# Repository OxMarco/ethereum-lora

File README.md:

# Ethereum LoRa

## Abstract

**Ethereum LoRa is a project aimed at adding a LoRa radio interface to Ethereum nodes.** By doing so, it becomes possible to query a node with JSON-RPC commands even in locations where Wi-Fi or cellular connectivity is absent. This enhancement allows Ethereum-based services to run in rural or underdeveloped areas of the world, fostering crypto adoption.

### About LoRa

The LoRa Communication System is an innovative project designed to facilitate seamless and efficient communication using the LoRa protocol. Aimed at establishing a reliable medium for data transmission even in challenging conditions, our solution stands as a testament to the powerful blend of software ingenuity and hardware capabilities. Whether it's for remote sensing applications, IoT devices, or any scenario where traditional connectivity might falter, our system ensures that your data reaches its destination.

## Technical Details

The software interfaces with the Ethereum node and the LoRa E22 module, allowing bi-directional communication. When the system starts, it sets up the LoRa module with specific configurations. Users can input JSON payloads, which are then sent via the LoRa interface to an Ethereum node. The system also listens for incoming messages from the Ethereum node, which can then be parsed and presented to the user.

### How It Works
At its core, our system relies on the LoRa (Long Range) protocol, a patented digital wireless data communication technology. Through a combination of software controllers and hardware integrations, the system listens for incoming LoRa messages and parses them for further processing. Depending on the message type—whether it's a handshake or a request—the controller can efficiently interpret and respond to the data.

### Assumptions
- The devices used are compatible with the LoRa E22 chip model.
- The data communicated is structured in JSON format with specific fields, such as "message_type", to allow the system to differentiate between different types of messages.
- The environment variables are correctly set for chip model, serial port, and other necessary pins.

### Implementation
We've designed a modular approach, with a main driver program that leverages two key components: the `ConfigManager` and `LoRaController`. The `ConfigManager` handles configuration retrieval while the `LoRaController` manages the setup, listening, and sending of LoRa messages. When data is received, it's parsed based on its message type and, if it's a request, further extracted to ensure clean and valid JSON content.

### Running the Project Locally

1. Ensure you have Python installed (version 3.x recommended).
2. Clone the repository:  
   ```
   git clone <repository_url>
   ```
3. Navigate to the project directory.
4. Install the required libraries:  
   ```
   pip install -r requirements.txt
   ```
5. Set the necessary environment variables (like `LORA_CHIP_MODEL`, `SERIAL_PORT`, etc.).
6. Run the application:  
   ```
   python client.py
   ```
   Or
   ```
   python server.py
   ```

## Hardware
The BOM is very basic, consisting of a LoRa UART module and a simple PCB TTL-to-UART adapter.

Pins at the bottom of the PCB allow users to upgrade the firmware or select a different working mode, for instance to support re-broadcasting, a form of basic mesh networking.

## Acknowledgements
A big thanks goes to the Ethereum Foundation for sponsoring this project under their "Run a Node" program.

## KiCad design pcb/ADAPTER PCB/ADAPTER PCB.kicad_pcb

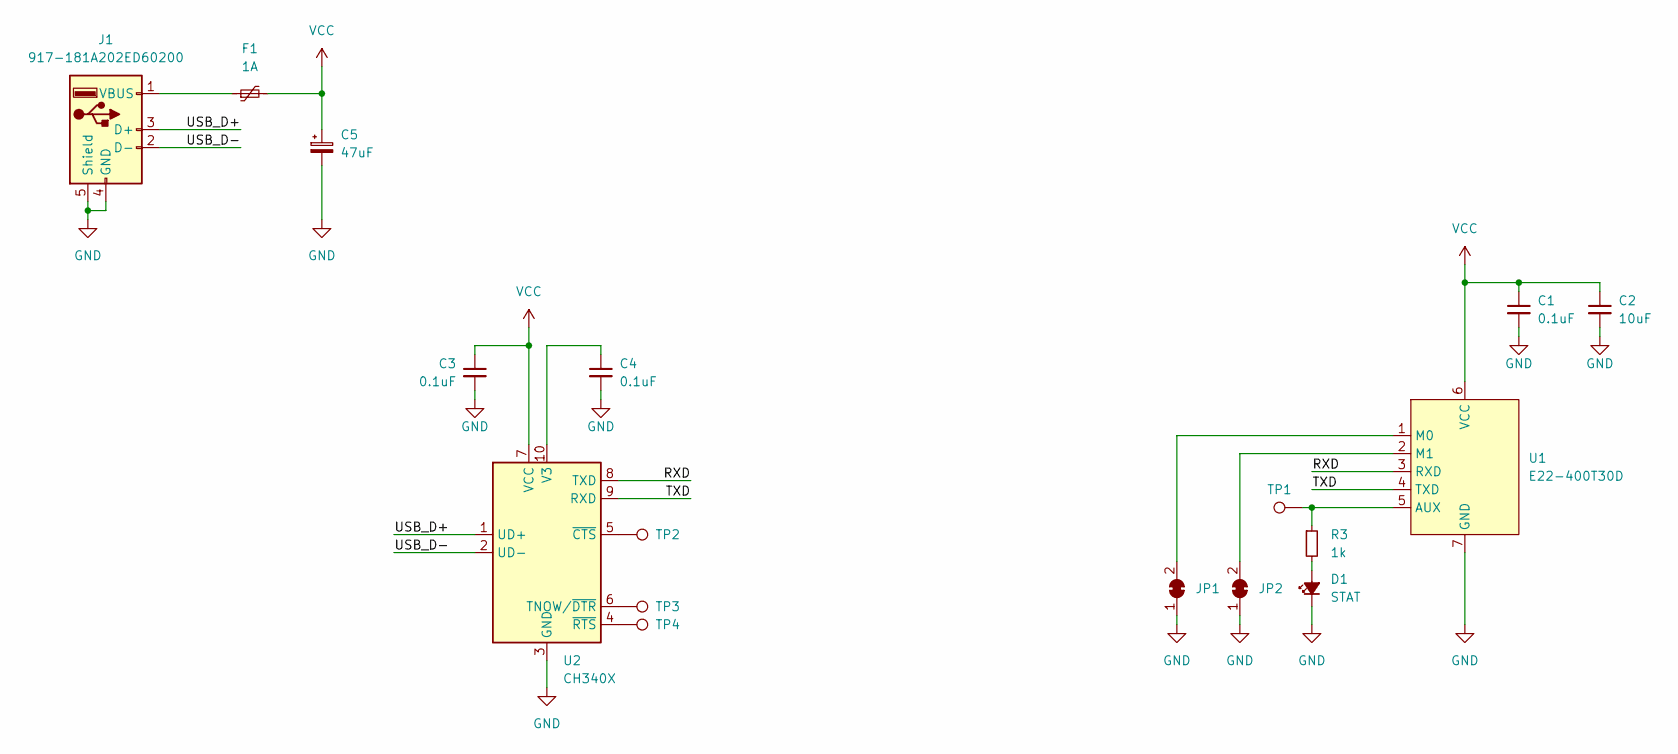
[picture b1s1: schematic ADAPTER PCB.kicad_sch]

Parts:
C1, C3, C4: 0.1uF; C_0603_1608Metric
C2: 10uF; C_0805_2012Metric
C5: 47uF; CP_EIA-3528-15_AVX-H
D1: STAT; LED_0603_1608Metric
F1: 1A; Fuse_0805_2012Metric
J1: 917-181A202ED60200; USB-A-TH_917-181A202ED60201
JP1: M0; PinHeader_1x02_P2.54mm_Horizontal
JP2: M1; PinHeader_1x02_P2.54mm_Horizontal
R3: 1k; R_0603_1608Metric
TP1, TP2, TP3, TP4: TestPoint; TestPoint_Pad_D1.0mm
U1: E22-400T30D; COMM-TH_E22-400T30D
U2: CH340X; MSOP-10_3x3mm_P0.5mm

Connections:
/RXD: U1.3 (RXD), U2.8 (TXD)
/TXD: U1.4 (TXD), U2.9 (RXD)
/USB_D+: J1.3 (D+), U2.1 (UD+)
/USB_D-: J1.2 (D-), U2.2 (UD-)
GND: C1.2, C2.2, C3.2, C4.2, C5.2, D1.1 (K), J1.4 (GND), J1.5 (Shield), JP1.1 (A), JP2.1 (A), U1.7 (GND), U2.3 (GND)
unnamed: D1.2 (A), R3.2
unnamed: F1.1, J1.1 (VBUS)
unnamed: JP1.2 (B), U1.1 (M0)
unnamed: JP2.2 (B), U1.2 (M1)
unnamed: R3.1, TP1.1, U1.5 (AUX)
unnamed: TP3.1, U2.6 (TNOW/~DTR)
unnamed: C4.1, U2.10 (V3)
unnamed: TP2.1, U2.5 (~CTS)
unnamed: TP4.1, U2.4 (~RTS)
VCC: C1.1, C2.1, C3.1, C5.1, F1.2, U1.6 (VCC), U2.7 (VCC)

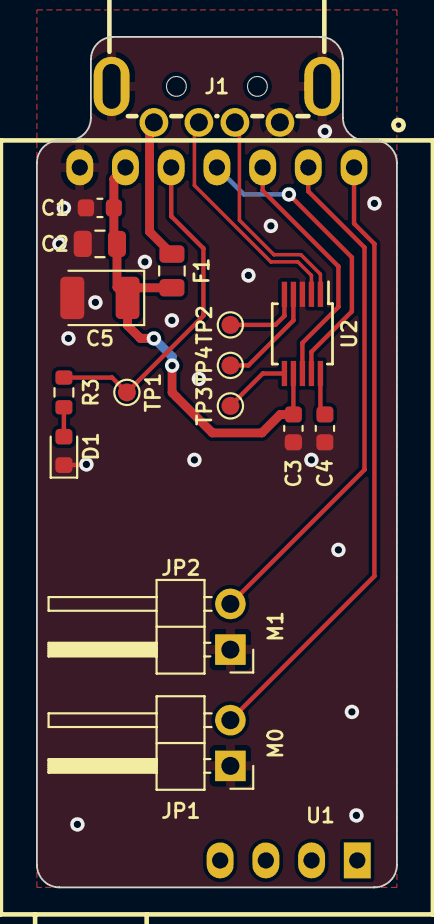
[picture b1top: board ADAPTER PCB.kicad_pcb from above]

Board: 2 copper layers, 20.0 x 47.2 mm, 17 parts (0 on the bottom side), 15 nets.

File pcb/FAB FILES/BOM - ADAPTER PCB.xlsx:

Designator | Quantity | Comment | Footprint | LCSC Part # | EXTERNALLY SOURCED MPN
C1, C3, C4 | 3 | 0.1uF | 603 | C14663
C2 | 1 | 10uF | 805 | C440198
C5 | 1 | 47uF | Capacitor_Tantalum_SMD:CP_EIA-3528-15_AVX-H | C22036
D1 | 1 | STAT | 603 | C2286
F1 | 1 | 1A | 805 | C910823
J1 | 1 | 917-181A202ED60200 | Plugin | C2763083
JP1 | 1 | M0 | Push-Pull,P=2.54mm | C492410
JP2 | 1 | M1 | Push-Pull,P=2.54mm | C492410
R3 | 1 | 1k | 603
U2 | 1 | CH340X | MSOP-10 | CH340X

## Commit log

2023-08-16 initial
2023-08-16 added graphics
2023-08-16 added test
2023-08-16 replying to incoming message
2023-08-16 buffering
2023-08-26 configuration
2023-08-26 configuration error code
2023-08-26 fix config
2023-08-26 fix e22 library
2023-08-26 fix json payload transmission
2023-08-26 reply
2023-08-26 fix receive msg
2023-08-26 refactoring
2023-08-26 naming
2023-08-26 destination
2023-08-26 handshake
2023-08-27 readme
2023-10-02 add header image
2023-10-02 added header img
2023-10-02 ethereum foundation sponsorship acknowledgement
2023-10-12 new header
2024-03-11 add pcb
2024-03-20 Ethereum grantee call presentation - 20/03/2024
